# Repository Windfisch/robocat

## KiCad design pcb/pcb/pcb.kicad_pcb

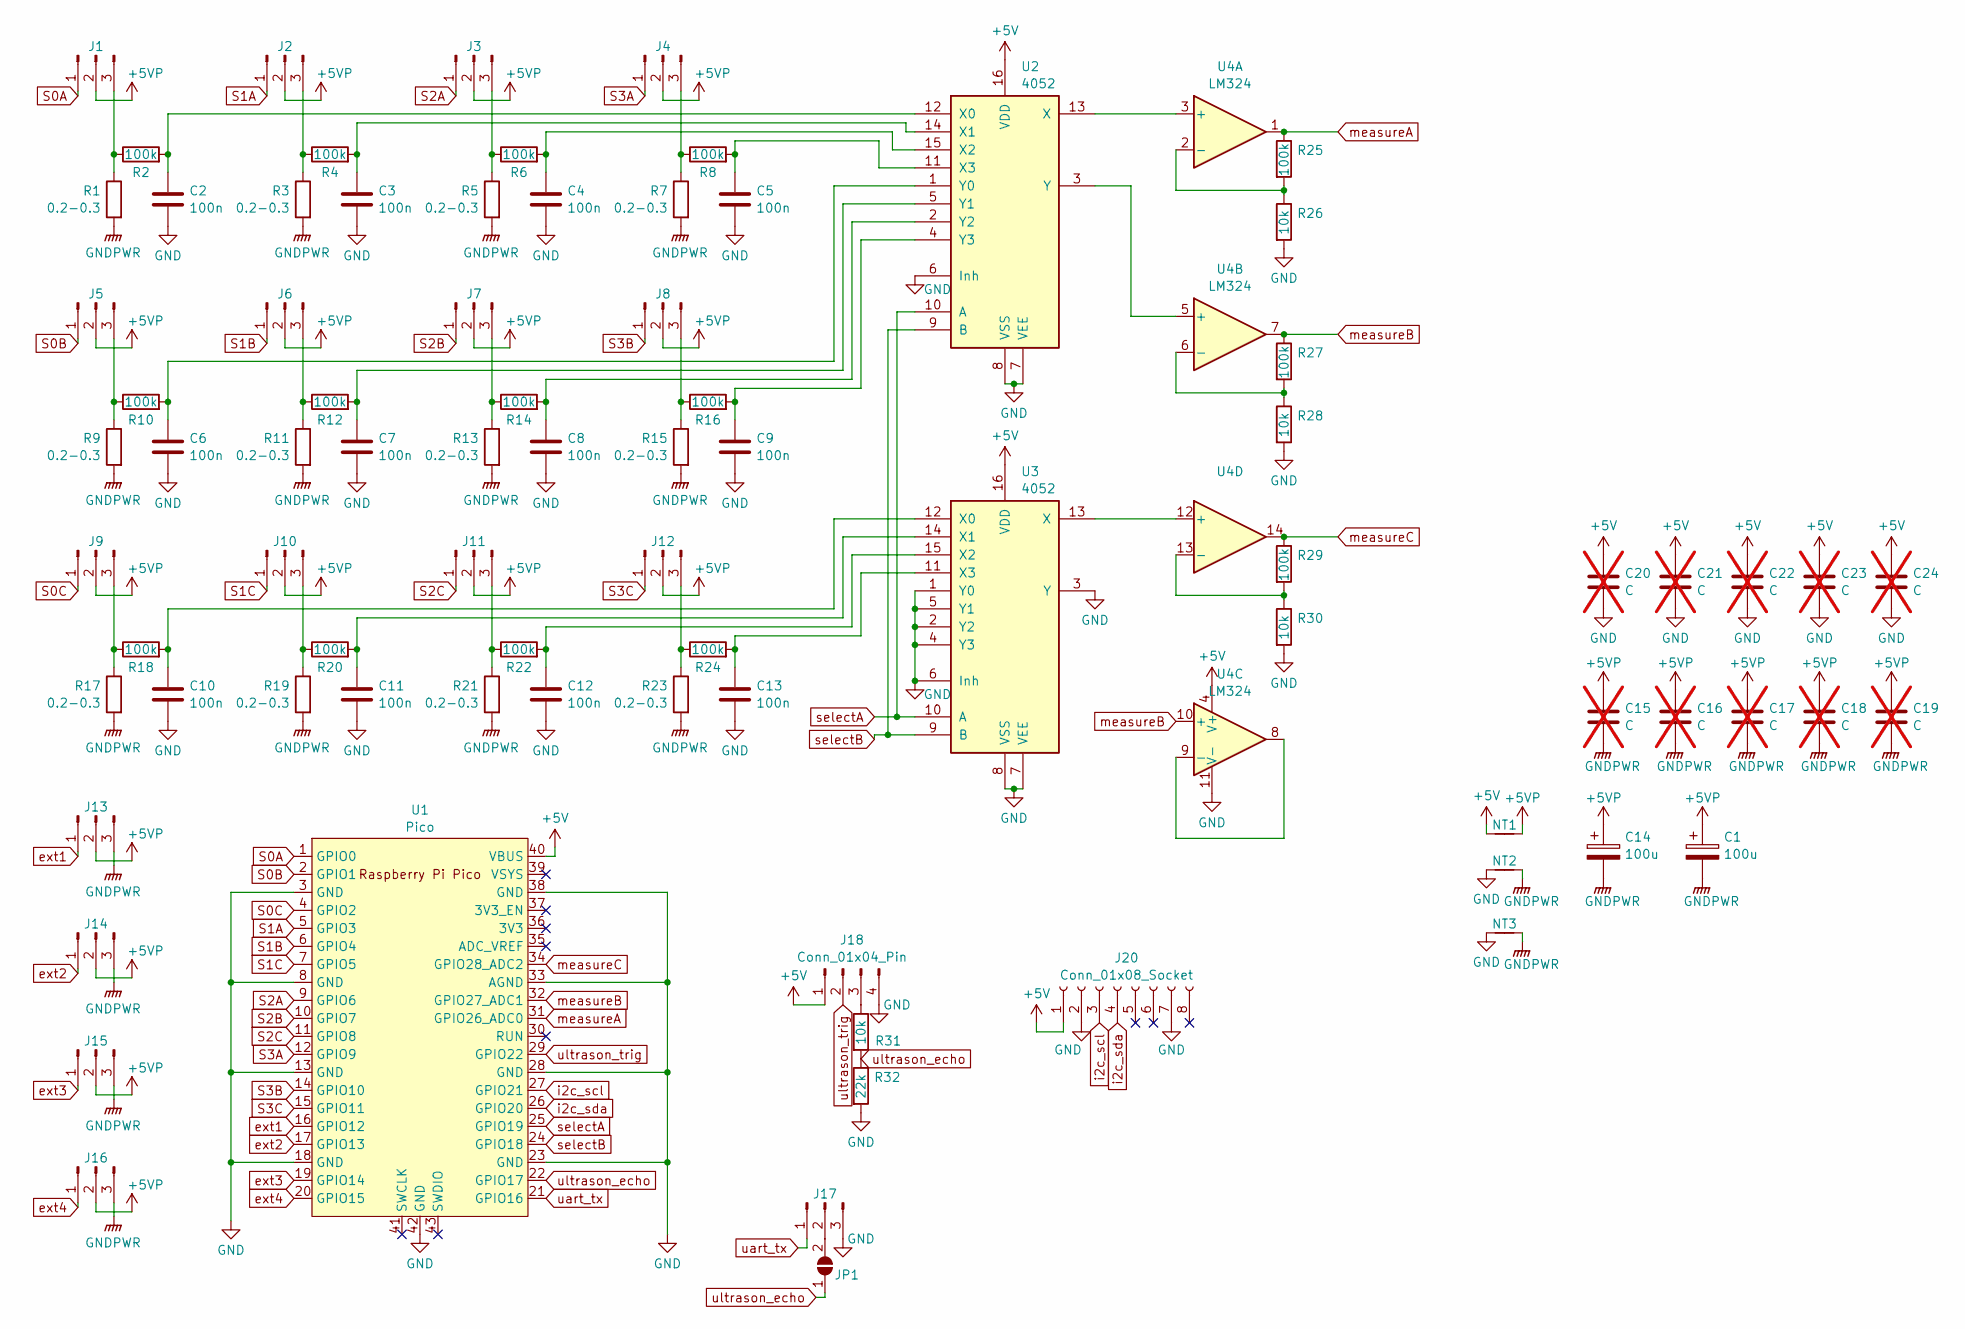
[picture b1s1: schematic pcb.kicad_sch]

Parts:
C1, C14: 100u; CP_Radial_D5.0mm_P2.50mm
C2, C3, C4, C5, C6, C7, C8, C9, C10, C11, C12, C13: 100n; C_0805_2012Metric
C15, C16, C17, C18, C19, C20, C21, C22, C23, C24: C; C_0805_2012Metric; not fitted
J1, J2, J3, J4, J5, J6, J7, J8, J9, J10, J11, J12, J13, J14, J15, J16, J17: Conn_01x03_Pin; PinHeader_1x03_P2.54mm_Vertical
J18: Conn_01x04_Pin; PinHeader_1x04_P2.54mm_Vertical
J20: Conn_01x08_Socket; GY-521
JP1: SolderJumper_2_Open; SolderJumper-2_P1.3mm_Open_Pad1.0x1.5mm
NT1, NT2, NT3: NetTie_2; NetTie-2_SMD_Pad0.5mm
R1, R3, R5, R7, R9, R11, R13, R15, R17, R19, R21, R23: 0.2-0.3; R_0805_2012Metric
R2, R4, R6, R8, R10, R12, R14, R16, R18, R20, R22, R24, R25, R27, R29: 100k; R_0805_2012Metric
R26, R28, R30, R31: 10k; R_0805_2012Metric
R32: 22k; R_0805_2012Metric
U1: Pico; RPi_Pico_SMD_TH
U2, U3: 4052; DIP-16_W7.62mm
U4: LM324; DIP-14_W7.62mm

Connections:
+5V: C20.1, C21.1, C22.1, C23.1, C24.1, J18.1, J20.1, NT1.1, U1.40 (VBUS), U2.16 (VDD), U3.16 (VDD), U4.4 (V+)
+5VP: C1.1, C14.1, C15.1, C16.1, C17.1, C18.1, C19.1, J1.2, J2.2, J3.2, J4.2, J5.2, J6.2, J7.2, J8.2, J9.2, J10.2, J11.2, J12.2, J13.2, J14.2, J15.2, J16.2, NT1.2
GND: C2.2, C3.2, C4.2, C5.2, C6.2, C7.2, C8.2, C9.2, C10.2, C11.2, C12.2, C13.2, C20.2, C21.2, C22.2, C23.2, C24.2, J17.3, J18.4, J20.2, J20.7, NT2.1, NT3.1, R26.2, R28.2, R30.2, R32.2, U1.3 (GND), U1.8 (GND), U1.13 (GND), U1.18 (GND), U1.23 (GND), U1.28 (GND), U1.33 (AGND), U1.38 (GND), U1.42 (GND), U2.6 (Inh), U2.7 (VEE), U2.8 (VSS), U3.1 (Y0), U3.2 (Y2), U3.3 (Y), U3.4 (Y3), U3.5 (Y1), U3.6 (Inh), U3.7 (VEE), U3.8 (VSS), U4.11 (V-)
GNDPWR: C1.2, C14.2, C15.2, C16.2, C17.2, C18.2, C19.2, J13.3, J14.3, J15.3, J16.3, NT2.2, NT3.2, R1.2, R3.2, R5.2, R7.2, R9.2, R11.2, R13.2, R15.2, R17.2, R19.2, R21.2, R23.2
unnamed: J1.3, R1.1, R2.1
unnamed: J2.3, R3.1, R4.1
unnamed: J3.3, R5.1, R6.1
unnamed: J4.3, R7.1, R8.1
unnamed: J5.3, R9.1, R10.1
unnamed: J6.3, R11.1, R12.1
unnamed: J7.3, R13.1, R14.1
unnamed: J8.3, R15.1, R16.1
unnamed: J9.3, R17.1, R18.1
unnamed: J10.3, R19.1, R20.1
unnamed: J11.3, R21.1, R22.1
unnamed: J12.3, R23.1, R24.1
unnamed: J17.2, JP1.2 (B)
unnamed: J18.3, R31.1
unnamed: C2.1, R2.2, U2.12 (X0)
unnamed: C3.1, R4.2, U2.14 (X1)
unnamed: C4.1, R6.2, U2.15 (X2)
unnamed: C5.1, R8.2, U2.11 (X3)
unnamed: U2.13 (X), U4.3 (+)
unnamed: C6.1, R10.2, U2.1 (Y0)
unnamed: C7.1, R12.2, U2.5 (Y1)
unnamed: C8.1, R14.2, U2.2 (Y2)
unnamed: C9.1, R16.2, U2.4 (Y3)
unnamed: U2.3 (Y), U4.5 (+)
unnamed: C10.1, R18.2, U3.12 (X0)
unnamed: C11.1, R20.2, U3.14 (X1)
unnamed: C12.1, R22.2, U3.15 (X2)
unnamed: C13.1, R24.2, U3.11 (X3)
unnamed: U3.13 (X), U4.12 (+)
unnamed: R25.2, R26.1, U4.2 (-)
unnamed: R27.2, R28.1, U4.6 (-)
unnamed: U4.8, U4.9 (-)
unnamed: R29.2, R30.1, U4.13 (-)
S0A: J1.1, U1.1 (GPIO0)
S0B: J5.1, U1.2 (GPIO1)
S0C: J9.1, U1.4 (GPIO2)
S1A: J2.1, U1.5 (GPIO3)
S1B: J6.1, U1.6 (GPIO4)
S1C: J10.1, U1.7 (GPIO5)
S2A: J3.1, U1.9 (GPIO6)
S2B: J7.1, U1.10 (GPIO7)
S2C: J11.1, U1.11 (GPIO8)
S3A: J4.1, U1.12 (GPIO9)
S3B: J8.1, U1.14 (GPIO10)
S3C: J12.1, U1.15 (GPIO11)
ext1: J13.1, U1.16 (GPIO12)
ext2: J14.1, U1.17 (GPIO13)
ext3: J15.1, U1.19 (GPIO14)
ext4: J16.1, U1.20 (GPIO15)
i2c_scl: J20.3, U1.27 (GPIO21)
i2c_sda: J20.4, U1.26 (GPIO20)
measureA: R25.1, U1.31 (GPIO26_ADC0), U4.1
measureB: R27.1, U1.32 (GPIO27_ADC1), U4.7, U4.10 (+)
measureC: R29.1, U1.34 (GPIO28_ADC2), U4.14
selectA: U1.25 (GPIO19), U2.10 (A), U3.10 (A)
selectB: U1.24 (GPIO18), U2.9 (B), U3.9 (B)
uart_tx: J17.1, U1.21 (GPIO16)
ultrason_echo: JP1.1 (A), R31.2, R32.1, U1.22 (GPIO17)
ultrason_trig: J18.2, U1.29 (GPIO22)

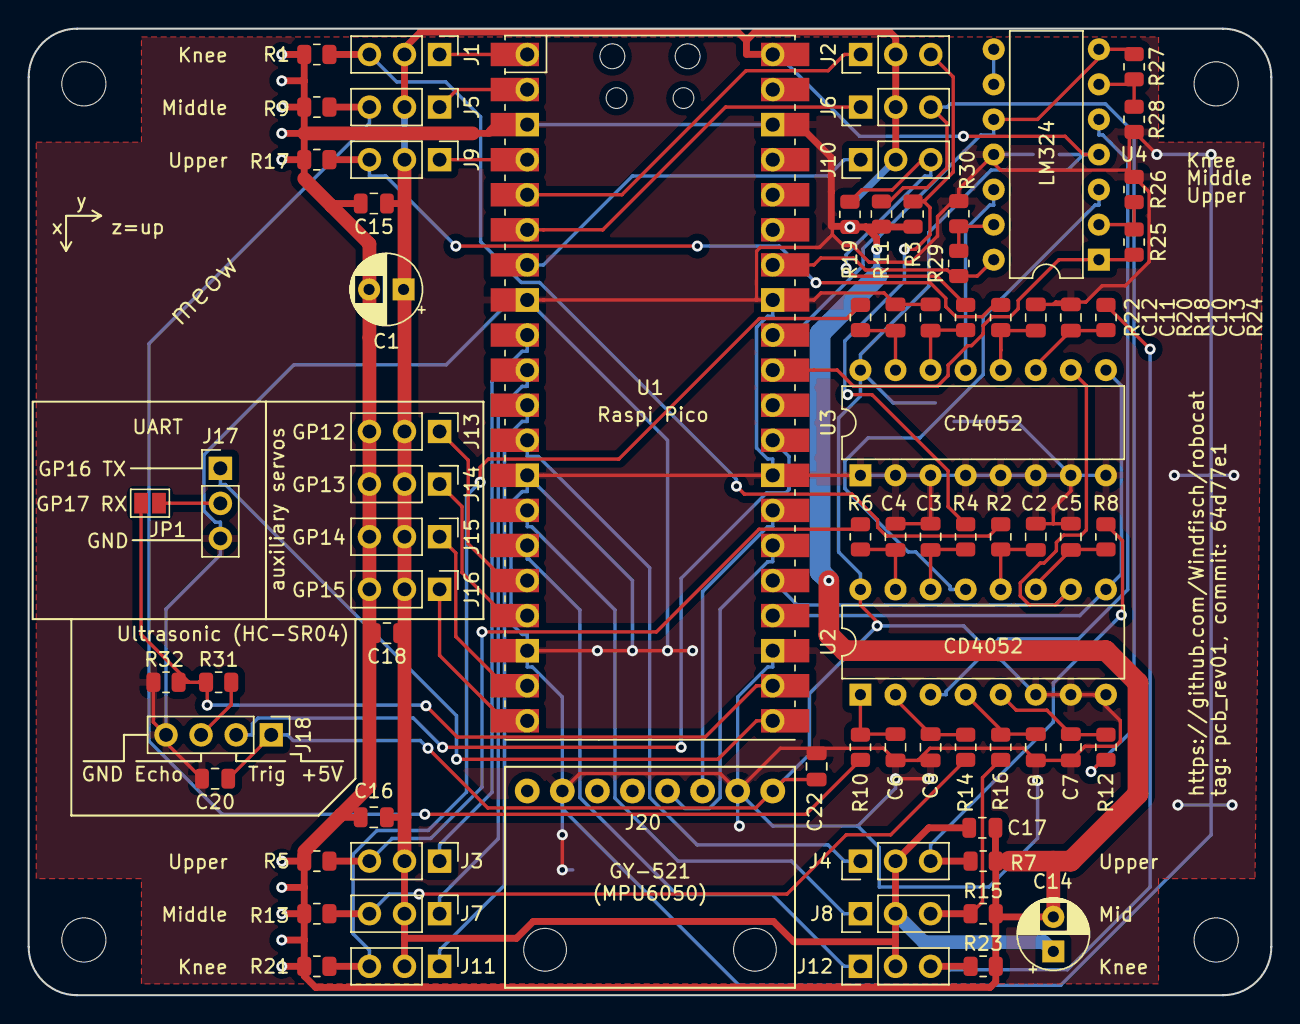
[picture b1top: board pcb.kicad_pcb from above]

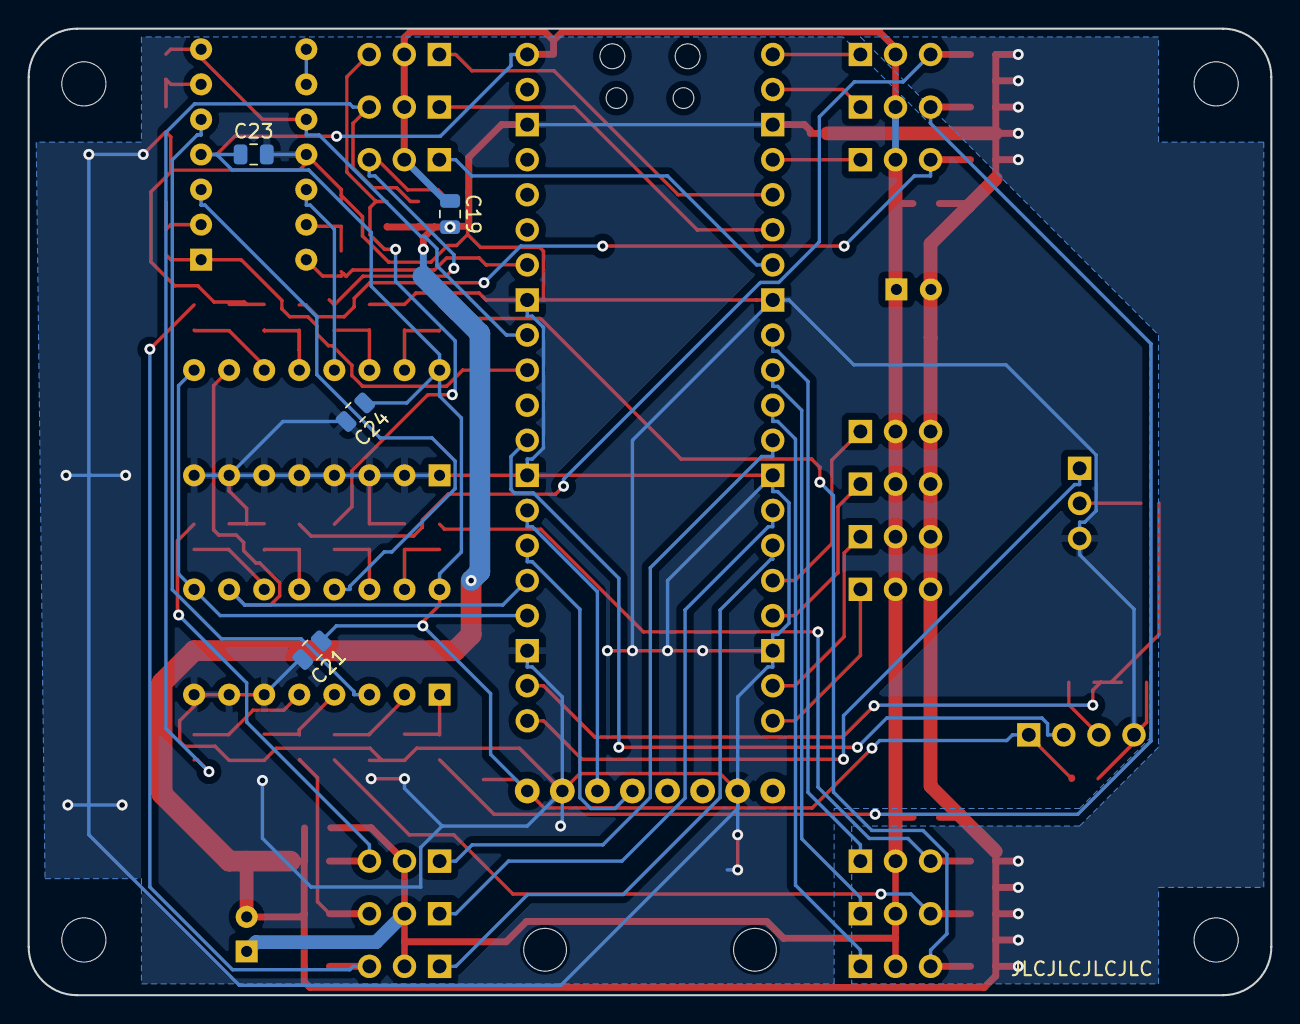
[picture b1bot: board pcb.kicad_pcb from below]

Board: 2 copper layers, 90.0 x 70.0 mm, 87 parts (4 on the bottom side), 63 nets.

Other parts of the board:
Hole1, Hole2, Hole3, Hole4: MountingHole_3.2mm_M3

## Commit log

2024-02-03 chamfer edge
2024-03-07 servo movement demo
2024-03-08 power sequencing
2024-03-10 walking
2024-05-10 first attempt
2024-05-10 cleanup pcb
2024-05-10 cleanup pcb2
2024-05-10 autoroute
2024-05-11 Final PCB revision, i guess?
2024-05-11 fillet corners
2024-05-12 final pcb rev01
2024-05-24 Initial CAD
2024-05-24 move code around
2024-05-24 Support backplate with hole for servo
2024-05-30 new chassis design
2024-05-30 firmware++, adjust to new pcb
2024-05-30 implement current measurement and keep all feet on the ground
    also makes the cat a kind-of-compliant mechanism
2024-05-31 inertial measurement
2024-06-08 fix paw-to-ground feature
2024-06-14 cascaded regulators
2024-07-13 robocat mk2 design with reinforced shoulders
2025-04-20 tiny cad adjustments
2025-04-20 leveling code
2025-04-20 add transport box
2025-04-20 pc control code
2025-04-21 Adjust standing position with dpad left/right
2025-04-25 WIP 2legged walking
2025-04-29 automatic leveling (PI-controller) when standing on two legs
2025-04-30 bit of tuning
2025-04-30 change inhibit_i
2025-04-30 walking!
2025-05-09 wip??
2025-06-09 requirements.txt
2025-06-18 changeable velocity
2025-06-18 fix dependencies
